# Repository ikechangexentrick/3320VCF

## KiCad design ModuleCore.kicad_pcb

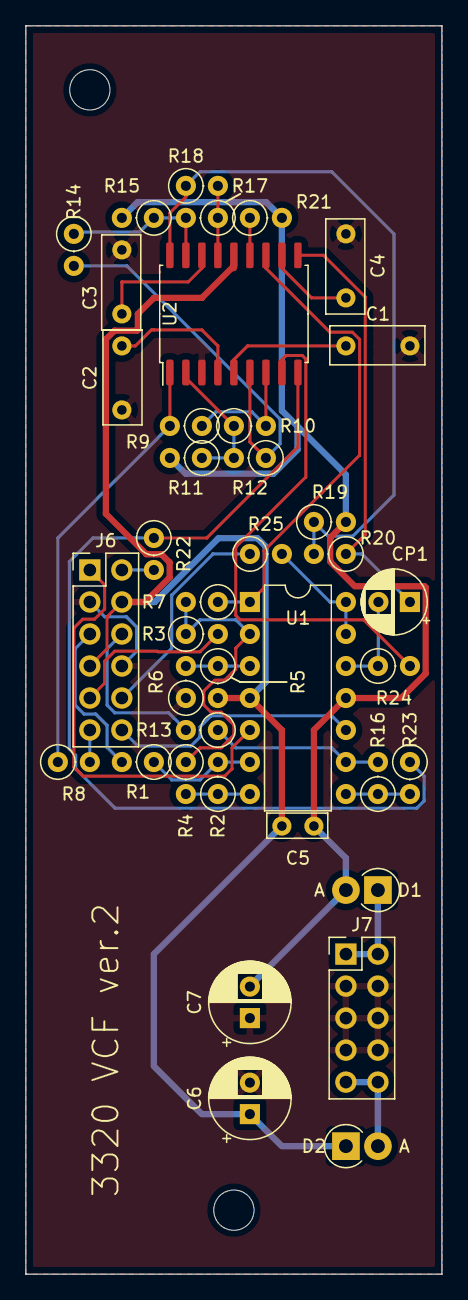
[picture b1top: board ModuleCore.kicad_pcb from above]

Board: 2 copper layers, 33.0 x 99.1 mm, 39 parts (0 on the bottom side), 37 nets.

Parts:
C1, C2, C3, C4: 300pF; C_Axial_L4.8mm_D3.1mm_P5.08mm_Horizontal
C5: 0.1uF; C_Axial_L4.8mm_D2.0mm_P2.54mm_Horizontal
C6, C7: 100uF; CP_Radial_D6.3mm_P2.50mm
CP1: 1uF; CP_Radial_D5.0mm_P2.50mm
D1, D2: 1N5819; D_DO-41_SOD81_P2.54mm_Vertical_AnodeUp
J6: interface_to_core; PinHeader_2x06_P2.54mm_Vertical
J7: power_bus; PinHeader_2x05_P2.54mm_Vertical
R1, R2, R3, R4, R5, R9, R12, R13, R16, R17, R20, R22, R23: 100k; R_Axial_DIN0207_L6.3mm_D2.5mm_P2.54mm_Vertical
R6, R25: 1k; R_Axial_DIN0207_L6.3mm_D2.5mm_P2.54mm_Vertical
R7, R21: 1.5k; R_Axial_DIN0207_L6.3mm_D2.5mm_P2.54mm_Vertical
R8, R10, R14, R18: 91k; R_Axial_DIN0207_L6.3mm_D2.5mm_P2.54mm_Vertical
R11, R15, R19: 220k; R_Axial_DIN0207_L6.3mm_D2.5mm_P2.54mm_Vertical
R24: 51k; R_Axial_DIN0207_L6.3mm_D2.5mm_P2.54mm_Vertical
U1: TL074; DIP-14_W7.62mm
U2: v3320; SOIC-18W_7.5x11.6mm_P1.27mm

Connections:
+12V: C5.1, C6.1, D2.1, J6.4, J6.7, R5.2, U1.4, U2.14
-12V: C5.2, C7.2, D1.2, R11.2, R15.2, R19.2, R21.2, U1.11
/Core/audio_in: J6.11, R8.2
/Core/audio_out: J6.10, R25.1
/Core/freq_cv: J6.5, R1.2
/Core/freq_cv_c: J6.1, U1.5
/Core/freq_knob: J6.9, R3.2
/Core/res_cv: J6.6, R13.2
/Core/res_cv_c: J6.12, U1.10
/Core/res_knob: J6.2, R22.2
GND: C1.2, C2.2, C3.2, C4.2, C6.2, C7.1, J6.3, J6.8, J7.3, J7.4, J7.5, J7.6, J7.7, J7.8, R6.1, U2.3
unnamed: C1.1, U2.5
unnamed: C2.1, U2.4
unnamed: C3.1, U2.16
unnamed: C4.1, U2.11
unnamed: CP1.1, R20.1, U2.10
unnamed: CP1.2, R24.1, U1.12
unnamed: D1.1, J7.1, J7.2
unnamed: D2.2, J7.9, J7.10
unnamed: R1.1, R2.2, U1.6
unnamed: R2.1, R4.2, U1.7
unnamed: R3.1, R4.1, R7.2, U1.2
unnamed: R5.1, R6.2, U1.3
unnamed: R7.1, U1.1, U2.12
unnamed: R8.1, R9.2, U2.1
unnamed: R10.1, R11.1, R12.2, U2.2
unnamed: R9.1, R10.2, U2.7
unnamed: R12.1, R14.2, U2.6
unnamed: R13.1, R16.2, U1.9
unnamed: R14.1, R15.1, R17.2, U2.17
unnamed: R16.1, R23.2, U1.8
unnamed: R17.1, R18.2, U2.15
unnamed: R18.1, R19.1, R20.2, U2.18
unnamed: R21.1, U2.13
unnamed: R22.1, R23.1, U2.9
unnamed: R24.2, U2.8
unnamed: R25.2, U1.13, U1.14

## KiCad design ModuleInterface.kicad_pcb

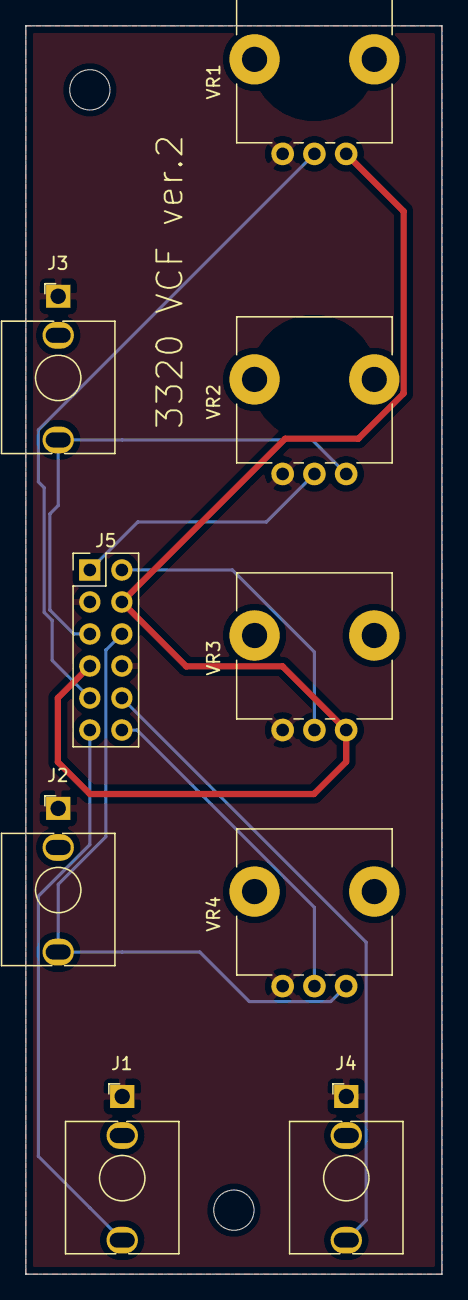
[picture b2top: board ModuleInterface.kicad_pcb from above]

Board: 2 copper layers, 33.0 x 99.1 mm, 9 parts (0 on the bottom side), 10 nets.

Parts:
J1: audio in; mono_jack_3.5mm
J2: res cv; mono_jack_3.5mm
J3: freq cv; mono_jack_3.5mm
J4: audio out; mono_jack_3.5mm
J5: interface_to_core; PinHeader_2x06_P2.54mm_Vertical
VR1: B10k; Potentiometer_Alps_RK09L_Single_Vertical
VR2, VR3, VR4: B100k; Potentiometer_Alps_RK09L_Single_Vertical

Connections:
+12V: J5.4, J5.7, VR1.3, VR3.3
/Interface/audio_in: J1.T, J5.11
/Interface/audio_out: J4.T, J5.10
/Interface/freq_cv: J3.T, J5.5, VR2.3
/Interface/freq_cv_c: J5.1, VR2.2
/Interface/freq_knob: J5.9, VR1.2
/Interface/res_cv: J2.T, J5.6, VR4.3
/Interface/res_cv_c: J5.12, VR4.2
/Interface/res_knob: J5.2, VR3.2
GND: J1.S, J2.S, J3.S, J4.S, J5.3, J5.8, VR1.1, VR2.1, VR3.1, VR4.1

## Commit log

2022-06-20 Improved the schematic: - fixed bugs in the pin orders of pots. - appened power reversal protection.
    PCB design version 2, included front panel also.
2022-06-20 version 1
